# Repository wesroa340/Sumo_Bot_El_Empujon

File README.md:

# Sumo_Bot_El_Empujon
Se está desarrollando un robot de combate de sumo autónomo, diseñado estrictamente bajo los parámetros del reglamento oficial (máximo 20x20 cm y 1 kg de masa total), optimizado para competir en el dohyo circular de 1.20 metros.

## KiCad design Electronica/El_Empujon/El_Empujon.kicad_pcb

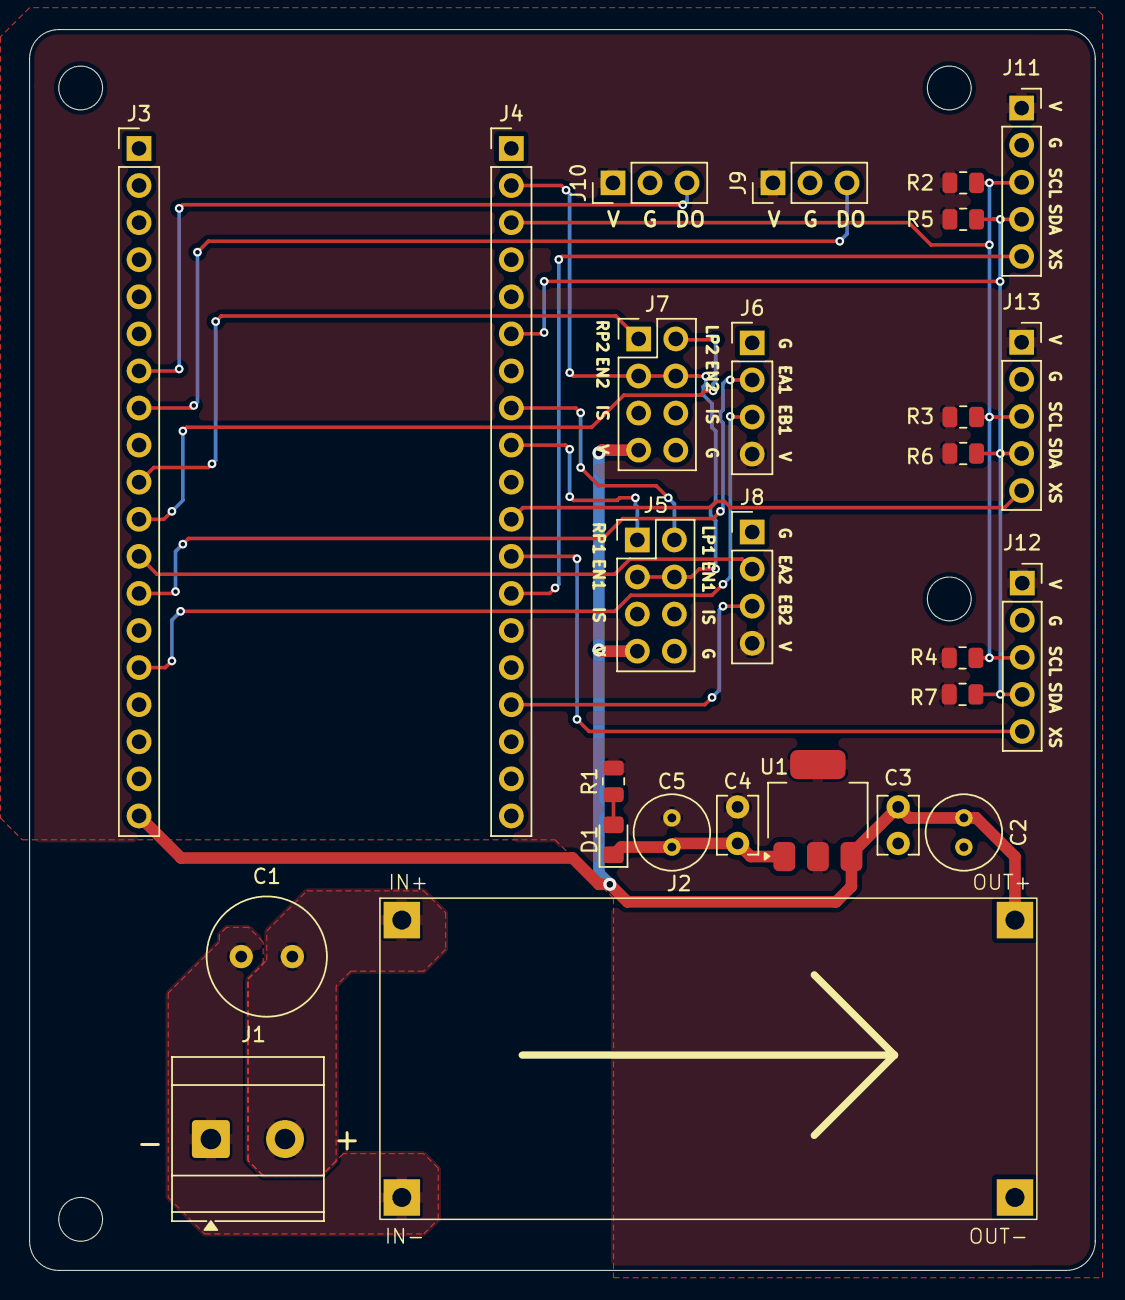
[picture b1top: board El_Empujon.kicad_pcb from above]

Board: 2 copper layers, 73.0 x 85.0 mm, 27 parts (0 on the bottom side), 22 nets.

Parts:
C1: 470uf/25V; C_Radial_D8.0mm_H7.0mm_P3.50mm
C2, C5: 10uF; C_Radial_D5.0mm_H7.0mm_P2.00mm
C3, C4: 100nF; C_Disc_D3.8mm_W2.6mm_P2.50mm
D1: LED; LED_0805_2012Metric_Pad1.15x1.40mm_HandSolder
J1: Screw_Terminal_01x02; TerminalBlock_MetzConnect_Type073_RT02602HBLU_1x02_P5.08mm_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
J2: Conn_01x04_Socket; PinSocket_1x04_P2.54mm_Vertical
J3, J4: Conn_01x19_Socket; PinHeader_1x19_P2.54mm_Vertical
J5, J7: Conn_01x08_Socket; PinHeader_2x04_P2.54mm_Vertical
J6, J8: Conn_01x04_Socket; PinHeader_1x04_P2.54mm_Vertical
J9, J10: Conn_01x03_Socket; PinHeader_1x03_P2.54mm_Vertical
J11, J12, J13: Conn_01x05_Socket; PinSocket_1x05_P2.54mm_Vertical
R1: 330; R_0805_2012Metric
R2, R3, R4, R5, R6, R7: 4.7K; R_0805_2012Metric
U1: AMS1117-3.3; SOT-223-3_TabPin2

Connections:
+3V3: C4.1, C5.1, J6.4, J8.4, J9.1, J10.1, J11.1, J12.1, J13.1, R1.2, R2.1, R3.1, R4.1, R5.1, R6.1, R7.1, U1.2 (VO)
+5V: C2.1, C3.1, J2.3, J3.19, J5.7, J7.7, U1.3 (VI)
+11V1: C1.1, J1.2, J2.1
/BTS7960/ENCA1: J3.13, J6.2
/BTS7960/ENCA2: J3.12, J8.2
/BTS7960/ENCB1: J3.15, J6.3
/BTS7960/ENCB2: J4.16, J8.3
/BTS7960/LPWM1: J4.8, J5.2
/BTS7960/LPWM2: J3.11, J7.2
/BTS7960/L_EN1: J4.2, J5.3, J5.4, J7.3, J7.4
/BTS7960/RPWM1: J4.9, J5.1
/BTS7960/RPWM2: J3.10, J7.1
/Esp32/GPIO4: J4.13, J11.5
/Esp32/GPIO16: J4.12, J12.5
/Esp32/GPIO17: J4.11, J13.5
/Esp32/GPIO21: J4.6, J11.4, J12.4, J13.4, R5.2, R6.2, R7.2
/Esp32/GPIO22: J4.3, J11.3, J12.3, J13.3, R2.2, R3.2, R4.2
/Esp32/GPIO32: J3.7, J10.3
/Esp32/GPIO33: J3.8, J9.3
GND: C2.2, C3.2, C4.2, C5.2, D1.1 (K), J2.4, J3.14, J4.1, J4.7, J5.8, J6.1, J7.8, J8.1, J9.2, J10.2, J11.2, J12.2, J13.2, U1.1 (GND)
GND2: C1.2, J1.1, J2.2
unnamed: D1.2 (A), R1.1

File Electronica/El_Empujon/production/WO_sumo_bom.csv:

Designator,Footprint,Quantity,Value,LCSC Part #
C1,C_Radial_D8.0mm_H7.0mm_P3.50mm,1,470uf/25V,
"C2, C5",C_Radial_D5.0mm_H7.0mm_P2.00mm,2,10uF,
"C3, C4",C_Disc_D3.8mm_W2.6mm_P2.50mm,2,100nF,
D1,0805,1,LED,
J1,TerminalBlock_MetzConnect_Type073_RT02602HBLU_1x02_P5.08mm_Horizontal,1,Screw_Terminal_01x02,
"J10, J9",PinHeader_1x03_P2.54mm_Vertical,2,Conn_01x03_Socket,
"J11, J12, J13",PinSocket_1x05_P2.54mm_Vertical,3,Conn_01x05_Socket,
J2,PinSocket_1x04_P2.54mm_Vertical,1,Conn_01x04_Socket,
"J3, J4",PinHeader_1x19_P2.54mm_Vertical,2,Conn_01x19_Socket,
"J5, J7",PinHeader_2x04_P2.54mm_Vertical,2,Conn_01x08_Socket,
"J6, J8",PinHeader_1x04_P2.54mm_Vertical,2,Conn_01x04_Socket,
R1,0805,1,330,
"R2, R3, R4, R5, R6, R7",0805,6,4.7K,
U1,SOT-223-3_TabPin2,1,AMS1117-3.3,
